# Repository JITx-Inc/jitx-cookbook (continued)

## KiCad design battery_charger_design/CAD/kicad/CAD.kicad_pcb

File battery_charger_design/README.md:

# Battery Charger PSU Cookbook Recipe

This tutorial guides you in creating a Lithium Polymer Battery Charging Board in JITX from the ground up. With step-by-step instructions, even individuals with no prior experience in JITX can learn to define hardware in software and generate a PCB using code.

### Picture of the final design:

### Resources

This board is fully open source, and available here: [Battery Charger Board JITX Recipe](https://github.com/JITx-Inc/jitx-cookbook/tree/main/battery_charger_design)

Clone this repo and open it in VSCode to follow along.

### Intended functionality

Let's start by considering what we want our design to be able to do:

- charge a 3.7V lithium polymer battery from a USB cable
- safely stop charging the battery once it's full
- an indicator to tell us when the battery is charging
- provide an output voltage of 2.8V from either the battery or the USB cable. If the USB is plugged in, we want it to charge the battery while also providing the output voltage

### Implementation plan

To accomplish the above, we need a few components:

- a lithium battery charger IC, let's use the Texas Instruments [BQ2407x](https://www.ti.com/lit/ds/symlink/bq24076.pdf?HQS=dis-mous-null-mousermode-dsf-pf-null-wwe&ts=1674500300089&ref_url=https%253A%252F%252Fwww.mouser.com%252F)
- a USB-C connector
- some connectors for the battery and voltage out
- a switch to turn things on and off
- some LEDs for the status indicator
- a voltage regulator to provide our 2.8V out, let's use the Diodes Inc [AP2125](https://www.digikey.com/en/products/detail/diodes-incorporated/AP2125K-2-8TRG1/4470776)

### Getting started

To start, we'll need to setup JITX. We can follow this tutorial to get setup: https://docs-testing.jitx.com/faq/installationinstructions.html

Then, we need to create a new project. So let's run VSCode, select the JITX extension, and click "New Project".

Now we're ready to start designing the board.

NOTE: The code below is not the entire design. Refer to the [Github repo](https://github.com/JITx-Inc/jitx-cookbook/tree/main/battery_charger_design) for a full working design. Below, we describe the design flow and thought process behind designing this battery charger board.

### Components

We've identified some specific components that we want to use, namely the [BQ2407x](https://www.ti.com/lit/ds/symlink/bq24076.pdf?HQS=dis-mous-null-mousermode-dsf-pf-null-wwe&ts=1674500300089&ref_url=https%253A%252F%252Fwww.mouser.com%252F) and the [AP2125](https://www.digikey.com/en/products/detail/diodes-incorporated/AP2125K-2-8TRG1/4470776), alongside some other generic components.

JITX has built-in support for many basic components like capacitors, resistors, and LED's, so we'll be able to source those as we need them while designing. For the specific ICs we're using, we'll need to either find an existing component definition, or make that ourselves. For this tutorial, let's just make the component definitions ourselves.

#### Battery Charger Component

We'll be using the BQ2407x lithium battery charger module:

[BQ2407x Datasheet](https://www.ti.com/lit/ds/symlink/bq24076.pdf?HQS=dis-mous-null-mousermode-dsf-pf-null-wwe&ts=1674500300089&ref_url=https%253A%252F%252Fwww.mouser.com%252F)

###### Making a new component
The first thing we'll do is go to the JITX VSCode extension and click "New Component". Let's make a new directory, called `components`, where we can save all of our components.

Now that we've created the directory, JITX is asking for the name of the new component, let's call it `BQ24078RGTR`, which we've copied directly from the datasheet.

We now have a new component started, but it doesn't have any information defined. Before anything, let's open up the BQ2407x datasheet in our browser so we have the information available as we implement the component in JITX: [BQ2407x Datasheet](https://www.ti.com/lit/ds/symlink/bq24076.pdf?HQS=dis-mous-null-mousermode-dsf-pf-null-wwe&ts=1674500300089&ref_url=https%253A%252F%252Fwww.mouser.com%252F)

###### What is the purpose of this code?

Let's take a look at the new file that has been made under `components/BQ24078RGTR.stanza`. We can see it has various information, including name, description, MPN, reference prefix, symbol, and footprint.

This information provides a description of the component under development. At the top of the file, we have regular imports that allow us to use JITX in Stanza. Further down, the `pcb-component` is the actual component that we're making. The `pcb-landpattern` is the landpattern (the footprint) of the component. Within the `pcb-component`, we have a table called pin-properties, which describes all of the pins of our component.

###### Filling out component values

Let's start by filling out information about the component itself. We can change the name, description, mpn, manufacturer, and reference-prefix to the information that makes sense for our component.

```
  name = "BQ24078RGTR"
  description = "Charger IC Lithium Ion 16-VQFN (3x3)"
  mpn = "BQ24078RGTR"
  manufacturer = "TI"
  reference-prefix = "U"
```

###### Assigning a footprint

We can inspect the line that says `assign-landpattern`. This is where the component's footprint is assigned. We can see that `lp-test-comp` is assigned by default. If we scroll up to the `lp-test-comp` landpattern, we can see that we're generating an SOIC footprint with the `make-n-pin-soic-landpattern` function. Looking at our datasheet, the BQ2407 uses a QFN footprint, so let's change the footprint to that.

In order to learn how to generate a QFN landpattern, let's move over to the docs here: https://docs.jitx.com.

We can then use the search bar and look up something about what we're trying to do, like **"make a qfn"**. In the search results, there is a reference to the `make-qfn-landpattern` function which looks like the QFN counterpart. We can replace the previous `make-n-pin-soic-landpattern` with this new QFN function. Let's also use a slightly modified version of this function to fill in information like the EP. We can find the extended version of the function, with EP, by searching for `make-qfn-landpattern` in [OCDB](https://github.com/JITx-Inc/open-components-database) and looking at the function options.

###### Creating Pins

Now we will define the pins of our component. This essentially maps pin names (which we can take from the datasheet, or make up) to the pads that are define in the footprint that we've assigned.

```
  pin-properties :
    [pin:Ref | pads:Ref ... | side:Dir ]
    [TS      | p[1]         | Left     ]
    [OUT     | p[10] p[11]  | Right    ]
    [ILIM    | p[12]        | Right    ]
    ...
```

###### Custom Properties

Let's also create some custom properties of our component that will help us later on. Let's give our component an LCSC vendor product number and a link to the datasheet:

```
  property(self.LCSC) = "C473396"
  property(self.datasheet) = "https://item.szlcsc.com/191835.html"
```

###### Defining a module

The BQ2407x has some pullups/pulldowns, bypass capacitors, LEDs, and other aspects that are going to be identical in every design. We could just pull in the raw component into our main design and add those there. However, to make this reusable, let's define a module for our component, so that whenever a main design imports that module, the basic setup has already been done.

To do so, let's add a line to define our module, define the pins of the mdoule we want to expose, and to instantiate the BQ2407 component in our module:

```
public pcb-module module :
  port vin
  port vout
  port gnd
  port bat+
  port sysoff

  ; using the component definition from above:
  inst bq : components/BQ24078RGTR/component
```

###### Building the BQ2407 submodule circuit

Now, let's look at the reference design of the BQ2407x in the datasheet and implement the aspects which will be the same in any instantiation (pullups, caps, etc.).

To add a capacitor, we use:
```
cap-strap(vout, gnd, ["capacitance" => 4.7e-6 "min-rated-voltage" => 12.0])
  
```

To add a resistor, we can use: 
```
res-strap(bq.ILIM, gnd, 1.1e3)
```

To specify a no-connect, we use:
```
no-connect(bq.TMR)
```

###### Grouping

After doing that for all of the components, let's group this module in our schematic and layout:
```
schematic-group(self) = BQ24078
layout-group(self) = BQ24078
```

#### AP2125 LDO Component

For the AP2125 LDO component, we follow the exact same workflow as for the BQ2407 above.

[AP2125 Datasheet](https://www.diodes.com/assets/Datasheets/AP2125.pdf)

### Main Design

Now that our components are defined, we can define our design. This step is analogous to designing a schematic, but it's defined in code. We're going to pull in all of our components and connect them together.

First, we'll create the battery manager submodule, and start connecting it:
```
  ; create the battery manager IC, connect it
  inst battery-manager : components/BQ24078RGTR/module
  net BMOUT (battery-manager.vout)
  net (battery-manager.gnd GND)
```

Then, let's create a JST connector for our battery input, and connect that to the battery charger (see the full [Github repo](https://github.com/JITx-Inc/jitx-cookbook/tree/main/battery_charger_design) for this component definition). We will load in a JST connector that we created and placed in the components directory:
```
  ; create battery JST connector, connect it
  inst battery-connector : components/PH2_0-2PWB/component 
  net (battery-connector.gnd GND)
  net (battery-connector.power battery-manager.bat+)
```

We also create a battery component. Importantly, this component won't actually be part of our final layout. The reason we create this is so that there is a voltage source logically defined that JITX can use later when we write checks. See the full [Github repo](https://github.com/JITx-Inc/jitx-cookbook/tree/main/battery_charger_design) for this component definition.
```
  ; create the battery itself
  inst battery : components/LithiumBattery/component(typ(3.7), 500.0) ; (voltage, current)
  net VBAT (battery.POWER battery-manager.bat+)
  net (GND battery.GND)
```

We can then do a very similiar thing to define the USB cable power source, the USB connector itself, and the output power JST.

Let's create a switch that can be used to turn the battery charger IC on and off. We'll pull one pole up, one pole down, and we'll make the common connection to the battery charger IC's SYSOFF pin:

```
  ; create switch and pull up, connect them. Switch pulls SYSOFF down for normal operation, high to disconnect battery
  inst switch-phy : components/MK-12C02-G025/component
  net (GND switch-phy.left switch-phy.gnd) ; switch turns battery-manager on
  net (switch-phy.center battery-manager.sysoff)
  val sys-r = res-strap(switch-phy.right, VBAT, 100.0e3) ; pull-up turns battery monitor off
```

Let's create the LDO, and connect it up to the rest of our circuit:
```
 ; create the LDO and connect it
  inst ldo : components/AP2125K-2_8TRG1/module
  net (BMOUT ldo.vin ldo.ce)
  net (ldo.gnd GND)
  net P2V8 (ldo.vout)
  val ldo-pulldown = res-strap(ldo.ce GND, 100.0e3) ; pull-down on the CE pin disables the LDO when the battery manager is not outputting voltage
```

We want to be able to test our board, so let's add some testpoints to the LDO voltage output:
```
  ; create test pads to test/solder LDO vout
  add-testpoint([vout-connector.power], Testpoint-SMDPad)
  add-testpoint([vout-connector.gnd], Testpoint-SMDPad)
```

To clean up our schematic, we can manually assign what type of symbol we want each net to take on:
```
  ; set symbols of some nets
  symbol(GND) = ocdb/utils/symbols/ground-sym
  symbol(VBAT) = ocdb/utils/symbols/supply-sym
  symbol(VBUS) = ocdb/utils/symbols/supply-sym
  symbol(BMOUT) = ocdb/utils/symbols/supply-sym
  symbol(P2V8) = ocdb/utils/symbols/supply-sym
```

Finally, let's clean up the schematic and layout by grouping together our subsystems:
```
  ; group some components in the schematic and layout to make it easier to read
  schematic-group([sys-r switch-phy battery-connector]) = schematic-group(battery-manager)
  layout-group([sys-r switch-phy battery-connector]) = layout-group(battery-manager)
  schematic-group([ldo ldo-pulldown]) = schematic-group(ldo)
  layout-group([ldo ldo-pulldown]) = layout-group(ldo)
```

Press `Ctrl+Enter`, and we have a fully functional schematic, and a board that is ready to be exported for layout! But first, let's write some checks to assess our board and make that everything works exactly as we'd expect it to.

### Checks

JITX has the ability to write checks for our designs. Before we even design a board, se can specify a number of various checks, like:

- which pins should be connected
- rated temperature of various components
- the input voltage range of a component
- etc.

###### Automated checks
The first step to adding design checking is in activating the built-in checks. Addin the following line at the end of our main design pcb-module:
```
  check-design(self)
```

And adding this line after the setup-board block
```
run-check-on-design(battery-manager-module)
```

tells JITX to run a number of automated checks on our board everytime we compile it.

###### Writing our own checks

We also have the capability to write our own checks to test for whatever we want. Let's add a check to the BQ2407x module to check that VSS and EP are connected, as the datasheet specifies this is a requirement.

First, we write a check that makes sure VSS exists, ensures EP exists, and then checks to make sure they're connected:
```
defn has-pin? (comp:JITXObject, pin-q:String) :
  val t = to-tuple $ for p in pins(comp) filter :
    substring?(to-string(ref(p)), pin-q)
  not empty?(t)

pcb-check bq2407-checks (component:JITXObject):

    #CHECK(
    name =                 "EP Exist check"
    description =          "Check that EP exists "
    condition =            has-pin?(component, "EP"),
    category =             "Component checks"
    subcheck-description =          "Check that the EP pin exists "
    pass-message =         "EP does exist. "
    fail-message =         "EP does not exist"
    locators =             [instance-definition(component)]
    )

    #CHECK(
    name =                 "VSS Exist check"
    description =          "Check that VSS exists "
    condition =            has-pin?(component, "VSS"),
    category =             "Component checks"
    subcheck-description =          "Check that the VSS pin exists "
    pass-message =         "VSS does exist. "
    info-message =         "VSS does not exist"
    locators =             [instance-definition(component)]
    )

    #CHECK(
    name =                 ""
    description =          "Check that EP is connected to GND/VSS"
    condition =            connected?([component.EP, component.VSS]),
    category =             "Connection"
    subcheck-description =          "Check that EP is connected to VSS"
    pass-message =         "EP is connected to VSS"
    fail-message =         "EP is not connected to VSS"
    locators =             [instance-definition(component)]
    )
```

In order to run this check whenever we use the BQ2407x module, we add the following line at the end of our BQ2407x `pcb-module` definition:
```
  check bq2407-checks(bq)
```

Now, everytime we use that module, our checks will make sure that's it's connected properly. Checkout the [Github repo](https://github.com/JITx-Inc/jitx-cookbook/tree/main/battery_charger_design) to see other checks we can use in our designs.

### Export to Kicad

We can export our design to Kicad using a single command that's already defined in our `helpers.stanza` which is included in our default new project.

Go to the bottom of your `main.stanza` and add this line, which will export our board to kicad:
```
export-design() 
```
### Layout
Layout your board exactly as you would normally in Kicad.

### Export from Kicad, order from JLCPCB

Install this plugin in Kicad to choose your components from LCSC and generate your PCB: https://github.com/Bouni/kicad-jlcpcb-tools

Upload your design to JLCPCB and order it:

### Conclusion

We've now successfully designed a PCB using JITX. You can now copy this workflow to design your own systems. To learn more, check out the other recipes in [the JITX Cookbook Recipes repo](https://github.com/JITx-Inc/jitx-cookbook) and read through the [tutorials](https://docs.jitx.com/tutorials/index.html) and [how-to guides](https://docs.jitx.com/howtoguides/index.html) in the JITX docs.

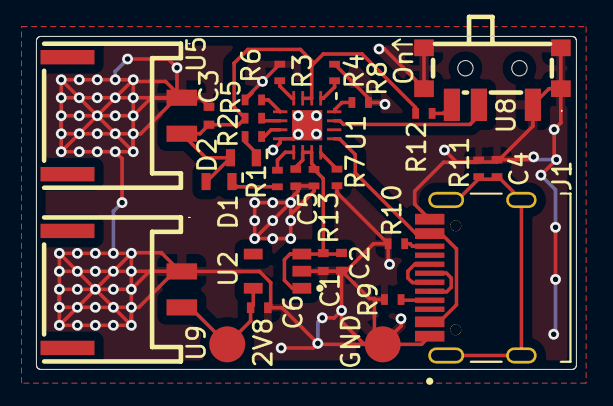
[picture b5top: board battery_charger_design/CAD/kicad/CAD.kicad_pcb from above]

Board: 2 copper layers, 30.0 x 18.5 mm, 27 parts (0 on the bottom side), 22 nets.

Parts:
C1, C2, C3: 4.7μF ± 20.00%; IPC_TWO_PIN_LANDPATTERN_3
C4: 100.0nF ± 10.00%; IPC_TWO_PIN_LANDPATTERN_1
C5, C6: 1.0μF ± 10.00%; IPC_TWO_PIN_LANDPATTERN_1
D1, D2: IPC_TWO_PIN_POL_LANDPATTERN
J1: LP_TYPE_C_31_M_12
R1, R2: 1.0kΩ ± 2.00%; IPC_TWO_PIN_LANDPATTERN_2
R3, R5, R6: 33.0Ω ± 2.00%; IPC_TWO_PIN_LANDPATTERN_2
R4: 10.0kΩ ± 2.00%; IPC_TWO_PIN_LANDPATTERN_2
R7: 1.1kΩ ± 0.50%; IPC_TWO_PIN_LANDPATTERN
R8: 2.7kΩ ± 0.50%; IPC_TWO_PIN_LANDPATTERN
R9, R10: 5.1kΩ ± 1.00%; IPC_TWO_PIN_LANDPATTERN
R11, R12, R13: 100.0kΩ ± 0.50%; IPC_TWO_PIN_LANDPATTERN
U1: VQFN_16_L30_W30_P050_BL_EP
U2: SOT95P280X145_5N
U5, U9: CONN_SMD_2P_P200_PH20_SPWB
U8: C778186

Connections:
BMOUT: C1.1, C2.1, C5.2, R13.1, U1.10, U1.11, U2.1, U2.3
CE#: R3.2, U1.4
CHG#: R1.1, U1.9
DN2: J1.A7, J1.B7
DP2: J1.A6, J1.B6
EN1: R5.1, U1.6
EN2: R6.1, U1.5
GND: C1.2, C2.2, C3.2, C4.2, C5.1, C6.1, J1.A1-B12, J1.B1-A12, R3.1, R4.2, R6.2, R7.2, R8.2, R9.2, R10.2, R11.2, R13.2, U1.8, U1.17, U2.2, U5.1, U8.1, U8.4, U8.5, U8.6, U8.7, U9.1
ILIM: R7.1, U1.12
ISET: R8.1, U1.16
P2V8: C6.2, U2.5, U9.2
PGOOD#: R2.1, U1.7
SYSOFF: U1.15, U8.2
TS: R4.1, U1.1
VBAT: C3.1, D1.a, D2.a, R5.2, R12.2, U1.2, U1.3, U5.2
VBUS: J1.A4-B9, J1.B4-A9, U1.13
c: D1.c, R1.2
good-power-led_c: D2.c, R2.2
rid_p1: J1.A5, R9.1
rid_rid_p1: J1.B5, R10.1
right: R12.1, U8.3
usb_rid_rid_p1: C4.1, J1.13, J1.14, J1.15, J1.16, R11.1

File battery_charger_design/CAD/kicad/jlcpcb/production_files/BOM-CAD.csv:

Comment,Designator,Footprint,LCSC
1.0kΩ ± 2.00%,"R1,R2",IPC_TWO_PIN_LANDPATTERN_2,C11702
2.7kΩ ± 0.50%,R8,IPC_TWO_PIN_LANDPATTERN,C138017
100.0nF ± 10.00%,C4,IPC_TWO_PIN_LANDPATTERN_1,C1525
~,J1,LP_TYPE_C_31_M_12,C165948
~,U2,SOT95P280X145_5N,C176953
33.0Ω ± 2.00%,"R3,R5,R6",IPC_TWO_PIN_LANDPATTERN_2,C25105
4.7μF ± 20.00%,"C1,C2,C3",IPC_TWO_PIN_LANDPATTERN_3,C255498
100.0kΩ ± 0.50%,"R11,R12,R13",IPC_TWO_PIN_LANDPATTERN,C25741
5.1kΩ ± 1.00%,"R10,R9",IPC_TWO_PIN_LANDPATTERN,C25905
1.0μF ± 10.00%,"C5,C6",IPC_TWO_PIN_LANDPATTERN_1,C29266
1.1kΩ ± 0.50%,R7,IPC_TWO_PIN_LANDPATTERN,C325543
~,U1,VQFN_16_L30_W30_P050_BL_EP,C473396
~,"U5,U9",CONN_SMD_2P_P200_PH20_SPWB,C47647
10.0kΩ ± 2.00%,R4,IPC_TWO_PIN_LANDPATTERN_2,C60490
~,U8,C778186,C778186
~,D1,IPC_TWO_PIN_POL_LANDPATTERN,C84263
~,D2,IPC_TWO_PIN_POL_LANDPATTERN,C965809

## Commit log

2023-01-26 setup repo, add readme, add draft of battery management board. Still need to setup OCDB globally
2023-01-26 Squashed 'open-components-database/' content from commit a280c57
    git-subtree-dir: open-components-database
    git-subtree-split: a280c57db19a21aba1edcc7838a21b9d0acfef9e
2023-01-26 refactor, so all recipes use ocdb subtree
2023-01-27 review battery_charger_design schematic and fix any issues, starting adding+running checks
2023-01-30 add component logic, add detailed checks, clean code, heavily comment for readability
2023-01-31 change landpatterns of components in battery charger board to use landpattern generators
2023-01-31 fix sot23-5 not defined error
2023-01-31 small changes interim checkin
2023-01-31 fixed logo location and merged main
2023-02-01 do first pass on battery charger layout
2023-02-01 finished design of battery charger board v0.1, MPNs assigned and PCBA files generated
2023-02-01 modify silkscreen aesthetically - v0.1 jlcpcb order
2023-02-02 feedback files from JLCPCB on fabrication
2023-02-04 started design of USB-C cable tester, programatically generating test LEDs
2023-02-07 programmatically placing parts based on the physical location of their pins
2023-02-08 usb cable tester: better software placement, test pad naming, add batter clip, ready for layout
2023-02-09 update CR2032 to have voltage supply pin, datasheet, LCSC
2023-02-09 usb cable tester testing submodules, running checks, naming nets manually, ready for layout
2023-02-10 simplify main code file, clean up based on PR comments, do first pass layout in Kicad
2023-02-10 add battery charger board recipe tutorial writeup and images
2023-02-13 make LEDs a module that generates voltage based on LED characteristics, comment complex code, add 2nd battery in series to work with normal LEDs.
2023-02-13 fix ballast resistor equation
2023-02-14 usb c cable tester - add voltage passthrough from batteries, custom 2 layer stackup, mounting holes, move around placement for autorouter, fix usb-c component
2023-02-15 usb-c battery tester - down to 1 battery, single sided, clean code, use usb-c without internal bridging, make modular, use relative placements, lots of comments
2023-02-16 Create LICENSE
2023-02-17 add test rig with usb cable, runs checks on test rig, update LEDs to run PowerPin checks on module pins
2023-02-18 update USB pin mapping algorithm to a snaking sort function for routability
2023-02-21 make snake-pin-sort generic so it can work on more than 2 rows
2023-02-21 usb-c cable tester - small changes for programmatic labelling of components, full layout
2023-02-21 update OCDB tracking to fixed usb commit
2023-02-22 usb c cable tester - update kicad project to have LCSC, generate JLCPCB gerbers and CPL, draft of final board order
2023-02-22 update proper JLCPCB smt info - rotations, LCSC, etc.
2023-02-23 usbc - cable tester - improve the snake sort and get-named-nets functions - kudos Philippe
2023-03-01 usb c tester - update to use parts-db for resistors
2023-03-03 usb c tester - switch to parts db resistor creation
2023-03-03 usb c tester - ready to order design with parts-db resistors and JLCPCB output
2023-03-09 usb-c cable tester - order v0p1 from JLCPCB
2023-03-10 usb-c tester - swap 0402 footprints, clean some comments, ready for recipe README addition
2023-03-10 update OCDB with usb-c bundle
2023-03-13 usb-c cable tester - swap large code block of making nets to a for loop with make-net
2023-03-14 add usb-c-tester README, update database-query to require rated-temperature
2023-03-21 move ble-mote into jitx-cookbook, restructure to follow recipe structure - checks and compiling working
2023-03-27 make blemote recipe writeup, add images
2023-03-27 update README to include blemote and explain what recipes are
2023-03-27 make OCDB submodule track the main branch
2023-03-27 update all designs to use set-current-design
2023-05-02 Add gpt generated python file
2023-05-02 Fix group naming
2023-05-02 Update gpt output
2023-05-02 Python parsing all pins in.
2023-05-02 Balls in, preparing for landpattern
2023-05-03 Depop calculated
2023-05-03 Final generated version
2023-05-19 add hackathon playground board
2023-05-22 change ports on USB to bundles so the pin names don't contain port prefix
2023-06-09 Fix typos and improve consistency of battery_charger_design
2023-06-23 Initial design for the sd card reader
2023-06-23 add ignore file
2023-06-26 Minor fixups for the layout
2023-06-26 attempted fix of Kicad project
2023-06-27 updated kicad and jlcpcb data - not reflected in jitx project
2023-07-01 Initial layout
2023-07-11 Add pull-down resistor and fix up KiCAD PCB
2023-07-12 Add imported VCO
2023-07-17 Change components to SMD and part of the layout
2023-07-17 Almost complete layout and showcase a bug
2023-07-24 Finalize design with simulation
2023-07-25 Finalize design and create a README
2023-07-25 Modify main README to add new recipe
2023-07-26 Add README and images
2023-07-28 Fix small issues and compartmentalize pcb-modules
2023-09-21 added component-status to ignore logo in BOM
2023-11-07 Add parts for pmic
2023-11-07 Testing design delay
2023-11-07 Fix typo
2023-11-07 Pre-routing
2023-11-16 initial new project
2023-11-16 deleted all local ocdb project files
2023-11-16 add a module for the HD3SS3220RNHR controller
2023-11-16 Updated USB3Converter Project
2023-11-16 WIP, new part
2023-11-18 added more modules to design
2023-11-20 updated usbc module
2023-11-20 imporant modules doen
2023-11-22 pushing small updates
2023-11-29 updated pmic design
2023-12-15 Added Schematic Dev folder with new parts
2023-12-20 made a new project folder with all components for USB design. ready for component placement and PCB routing. stackup and rules finished and applied.
2023-12-21 Remove extra folder
2023-12-21 Renaming folder
2023-12-21 Change ocdb version
2023-12-21 Remove extra copy of ocdb
2023-12-21 add root stanza.proj, rename usb-c things
2023-12-21 Fix usb-c cable tester
2023-12-21 Fixing type b connector
2023-12-21 Update connector and usb-2 conditioning models
2023-12-21 Reworked mux
2023-12-21 updated esd components
2023-12-21 Get code working
2023-12-22 added pin assignment
2024-01-23 New layout
2024-02-16 Make power regulator parametric
2024-02-21 Updated OCDB to temporary hacks branch
2024-02-21 [WIP] Adding Topology/Routing Structures for USB Converter
    While testing on SI-Integration (62cef5a9eee08) - I ran into the following
    problem.
    When Attempting to run `main.stanza` - I get an exception that seems to be related to pin assignment:
    ```
    stanza> reload
    Saving stable design and reference designator table
2024-02-21 [Bugfix] Removed reference to `Stackup`
2024-02-21 [Refactor] Added a function for managing swappable diff-pairs
2024-03-06 new check-in for regulator example design
2024-03-07 Added more SI tools to support topologies
2024-03-07 Initial Topology/SI implementation for the USB Converter
    This has some issues but this is a good milestone point:
    1. The structure application is not consistent because I can't properly apply
    the structure from the top level. It either needs to be passed in to the modules below or we need to move all the components to the top layer.
    2. The connector is currently type-B, we need to move to type-A
2024-03-08 [Refactor] Moved the pull-down and blocking capacitors to the top-level.
    In the current JITX runtime, adding the timing and structure constraints
    across a pcb-module hierarchy that uses pin assignment is awkward at best
    and impossible in this particular case.
    We will likely need a topology introspection ability to solve this in the general case.
2024-03-08 removed designs folder
2024-03-08 updated ignore file
2024-03-08 Refactor pin models to reduce uncertainty
    I currently don't have good models for the pins so I'm just
    setting them to zero for now.
2024-03-08 Added initial checkpoint for the USB A to C converter design
    This has all of the topologies, routing structures, and constraints
    setup to support a valid design as of git hash 350934303
2024-03-11 updated whole repo to run from root
2024-03-13 initial check point in cookbook
2024-03-13 some files for ambiq
2024-03-13 updated design, working on placement
2024-03-13 incremental placement
2024-03-14 crash check-point
2024-03-14 routing of regular signals almost done
2024-03-14 Keyboards
2024-03-14 updated ref-des, trace width-space, etc
2024-03-14 removed ever-mutating schematic files from git
2024-03-14 running from top coming soon
2024-03-14 now runs from the top level
2024-03-14 updated directory name
2024-03-14 added stable.design
2024-03-14 updated ocdb
2024-03-15 Sample keyboard layout
2024-03-15 added ambiq-demo
2024-03-15 layout progress
2024-03-15 Demo version
2024-03-15 added some new ignores
2024-03-18 Demoed version
2024-04-05 updated names to be more consistent
2024-04-09 updated with slm
2024-04-12 fixed filename ref
2024-04-12 added one more ignore entry
2024-04-12 fixed up the JITX reference for SLM (manually)
2024-04-12 removed designs folder from repo as it is version dependent
2024-04-15 Added tools for managing signal ends in topologies.
2024-04-15 Refactored the main design using Patrick's proposed method of signal ends
    This makes our design able to properly assign constraints to the end
    of a topology without needing all of the components in the topology to
    be at the top-level.
2024-04-15 Purged files that should not be part of the git repo
    These files don't contain actual design data.
2024-04-15 Added a gitignore file for the `designs` directory
2024-04-16 [WIP] Strange behavior in the schematic
    For Tristan
    https://jit-x.slack.com/archives/C04JX5ZKF9B/p1713302131108829
2024-04-16 [WIP] Schematic throws `impossible` error
2024-04-16 [WIP] BOM status not updating
2024-04-16 [WIP] Strange feedback divider behavior
2024-04-16 [WIP] Highlighting diff-pair in board seems off
2024-04-16 Updated the Buck Converter design to be more parametric.
2024-04-16 Moved TPS62082 to TPS6208x to make it clear that it uses any from the family.
2024-04-17 Updated various schematic symbols
    This cleans up the schematic and makes it more readable.
2024-04-17 [WIP] Key Error on group move
2024-04-17 fixed label placement
2024-04-17 removed ocdb
2024-04-17 removed ocdb submodule
2024-04-17 [WIP] Create large group that is very CPU intensive
2024-04-18 [WIP] Ratnest wire not showing topology
2024-04-19 [WIP] Unsat error on startup
2024-04-26 Updated the USB Mux symbol to be multi-bank
    This cleans up the schematic alot.
2024-04-26 [WIP] Saving state after Error
2024-05-02 Error blocking design from loading
2024-05-02 Diff pair neckdown
2024-05-02 Uninitialized error
2024-05-30 [WIP] - Trying to for a saner USB A to C converter
    This half-baked and not ready to distribute.
    It is only for an example of how I think we should do topologies
    for Bhusan.
2024-08-07 Updated Syntax for all symbols, stackups, and routing structures
2024-08-07 Updated the `pin -> port` syntax refactor
2024-11-08 tweaked landpattern layers
